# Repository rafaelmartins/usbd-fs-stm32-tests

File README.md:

# usbd-fs-stm32-tests

Integration tests for [usbd-fs-stm32](https://github.com/rafaelmartins/usbd-fs-stm32) library.

This repository contains the whole infrastructure required to test the library in real hardware:

- Raspberry PI Hat [PCB](./pcb) and [3D models](./3d-models)
- [Test Runner](./runner)
- [Test Firmware](./firmware) *(TODO)*
- [Github Action](./action.yml) used by main [usbd-fs-stm32 repository](https://github.com/rafaelmartins/usbd-fs-stm32) *(TODO)*

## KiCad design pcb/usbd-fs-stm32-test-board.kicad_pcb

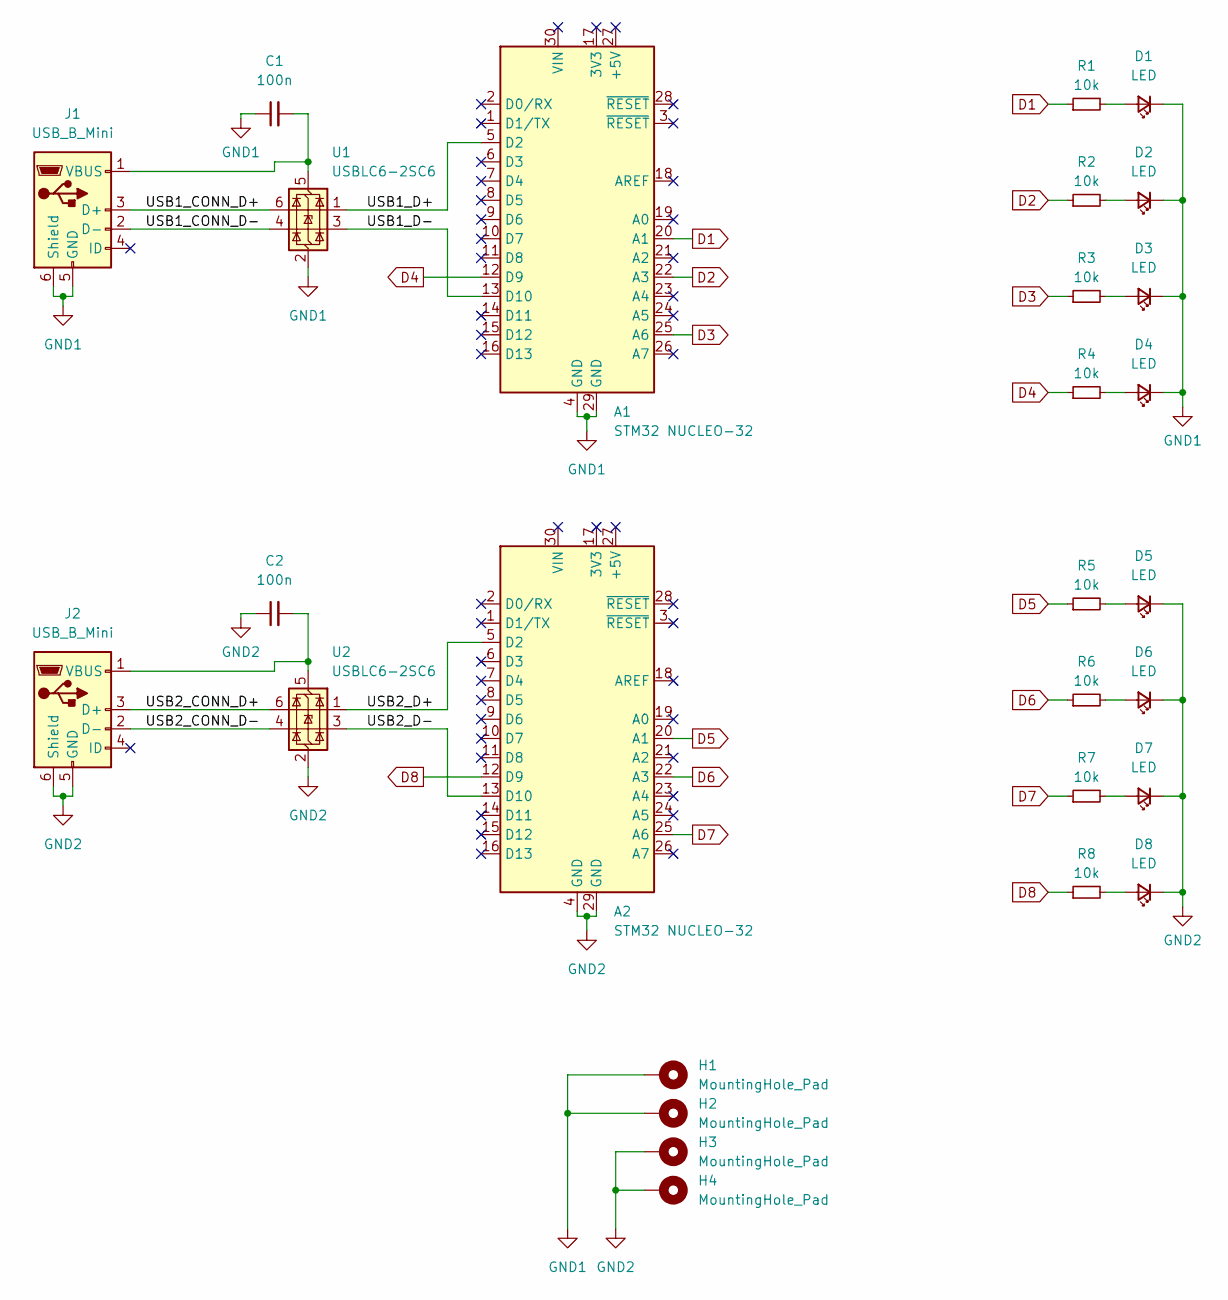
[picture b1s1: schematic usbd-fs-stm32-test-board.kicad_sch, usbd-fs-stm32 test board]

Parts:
A1, A2: STM32 NUCLEO-32; NUCLEO-32
C1, C2: 100n; C_TDK_FA28
D1, D2, D3, D4, D5, D6, D7, D8: LED; LED_D3.0mm
H1, H2, H3, H4: MountingHole_Pad; MountingHole_2.2mm_M2_Pad_Via
J1, J2: USB_B_Mini; USB_Mini-B_PTH
R1, R2, R3, R4, R5, R6, R7, R8: 10k; R_YAGEO_MFR-25FTE52_Horizontal
U1, U2: USBLC6-2SC6; SOT-23-6

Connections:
/USB1_CONN_D+: J1.3 (D+), U1.6 (I/O1)
/USB1_CONN_D-: J1.2 (D-), U1.4 (I/O2)
/USB1_D+: A1.5 (D2), U1.1 (I/O1)
/USB1_D-: A1.13 (D10), U1.3 (I/O2)
/USB2_CONN_D+: J2.3 (D+), U2.6 (I/O1)
/USB2_CONN_D-: J2.2 (D-), U2.4 (I/O2)
/USB2_D+: A2.5 (D2), U2.1 (I/O1)
/USB2_D-: A2.13 (D10), U2.3 (I/O2)
D1: A1.20 (A1), R1.1
D2: A1.22 (A3), R2.1
D3: A1.25 (A6), R3.1
D4: A1.12 (D9), R4.1
D5: A2.20 (A1), R5.1
D6: A2.22 (A3), R6.1
D7: A2.25 (A6), R7.1
D8: A2.12 (D9), R8.1
GND1: A1.4 (GND), A1.29 (GND), C1.1, D1.1 (K), D2.1 (K), D3.1 (K), D4.1 (K), H1.1, H2.1, J1.5 (GND), J1.6 (Shield), U1.2 (GND)
GND2: A2.4 (GND), A2.29 (GND), C2.1, D5.1 (K), D6.1 (K), D7.1 (K), D8.1 (K), H3.1, H4.1, J2.5 (GND), J2.6 (Shield), U2.2 (GND)
unnamed: D1.2 (A), R1.2
unnamed: D2.2 (A), R2.2
unnamed: D3.2 (A), R3.2
unnamed: D4.2 (A), R4.2
unnamed: D5.2 (A), R5.2
unnamed: D6.2 (A), R6.2
unnamed: D7.2 (A), R7.2
unnamed: D8.2 (A), R8.2
unnamed: C1.2, J1.1 (VBUS), U1.5 (VBUS)
unnamed: C2.2, J2.1 (VBUS), U2.5 (VBUS)

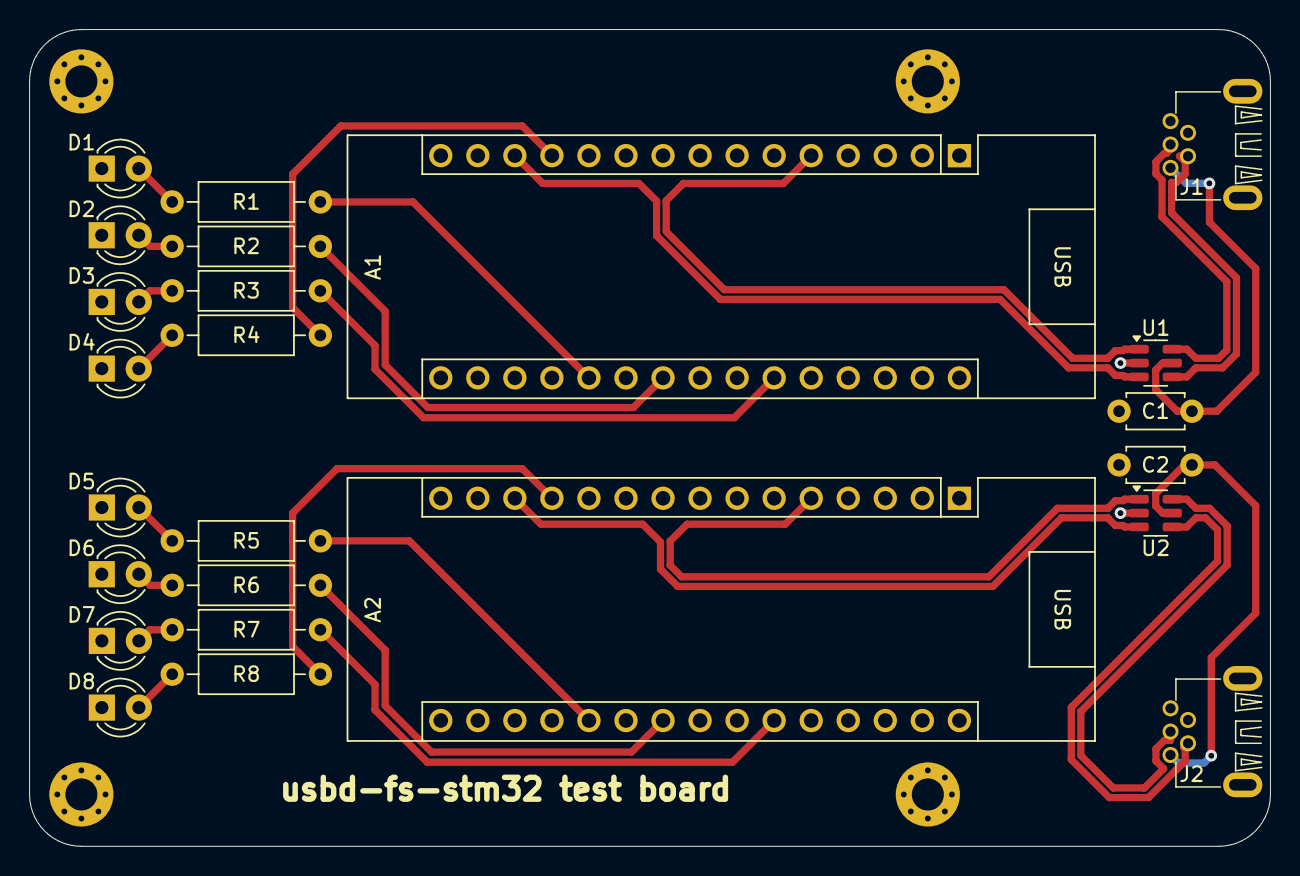
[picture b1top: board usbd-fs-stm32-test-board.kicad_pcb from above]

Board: 2 copper layers, 85.1 x 56.0 mm, 28 parts (0 on the bottom side), 28 nets.

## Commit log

2024-11-18 Initial commit
    I have this PCB waiting on my desk for months but finally assembled it.
    Let's get things started!
2024-11-19 runner: initial code, no actual tests yet
2024-11-19 runner: enable warnings and convert to error
2024-11-19 runner: move CMakeLists.txt to subfolder
2024-11-19 firmware: initial code, just a dumb blink test
2024-11-20 pcb: revision 20241120: fixed conflict of LED pins with VCP pins
2024-11-20 firmware: link against usbd-fs-stm32, move tests to root
2024-11-23 add -firmware suffix to firmware portion of tests
2024-11-23 firmware: changes to support pcb revision 20241120
2024-11-23 runner: reimplement in golang
2024-11-24 firmware: implement a half-arse hal. #whynot
2024-11-30 firmware: runner: implement serial protocol and firmware building
2024-12-01 allow test firmware to mark test as failed
    also rewrite most of the stlink implementation to not reuse connections
    and halt the devices after running tests.

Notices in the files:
pcb/usbd-fs-stm32-test-board.kicad_pcb:
Released under CERN Open Hardware Licence Version 2 - Strongly Reciprocal
